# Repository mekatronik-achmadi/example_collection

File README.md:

Examples collection from various works

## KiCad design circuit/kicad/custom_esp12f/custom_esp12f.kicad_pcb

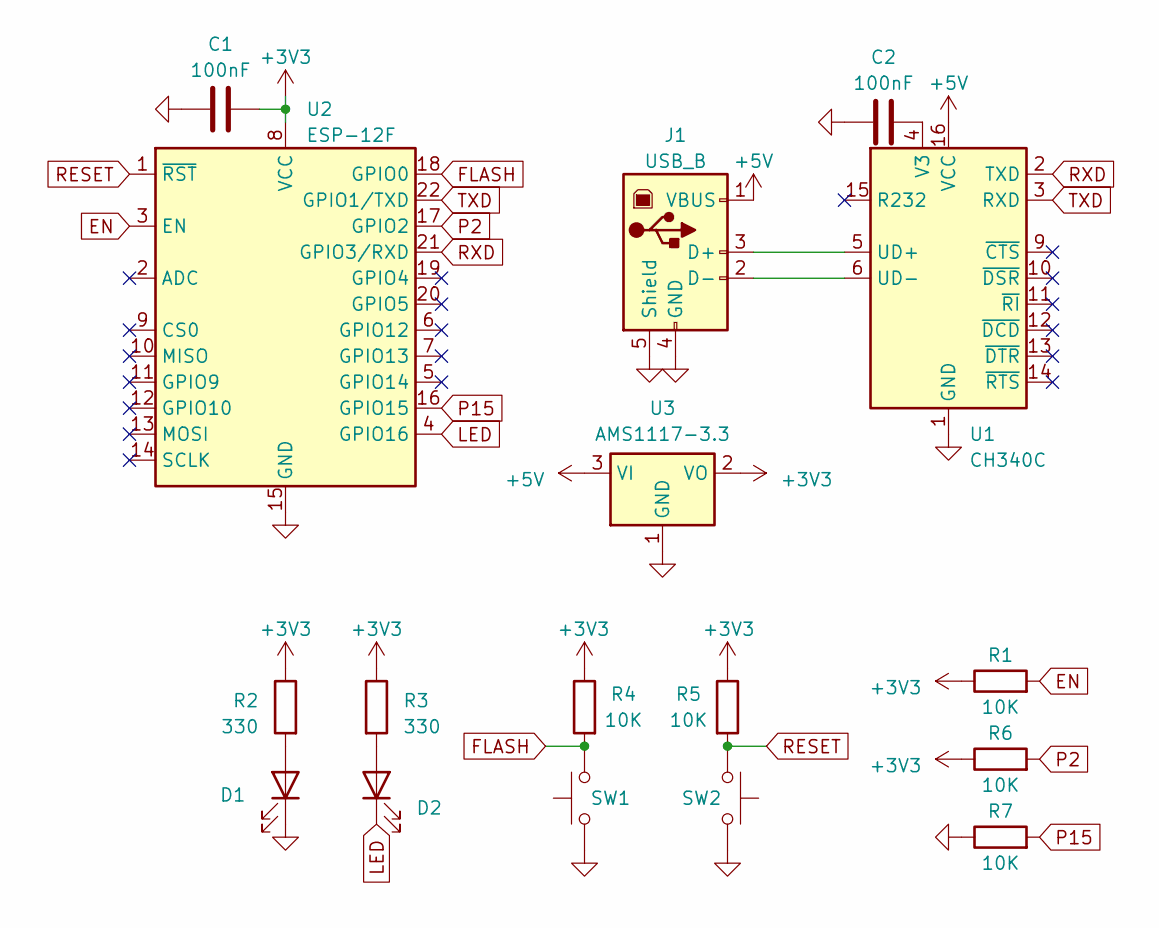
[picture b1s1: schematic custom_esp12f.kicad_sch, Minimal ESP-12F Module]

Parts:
C1, C2: 100nF; C_0805_2012Metric_Pad1.18x1.45mm_HandSolder
D1: MERAH; LED_0805_2012Metric_Pad1.15x1.40mm_HandSolder
D2: HIJAU; LED_0805_2012Metric_Pad1.15x1.40mm_HandSolder
J1: USB_B; USB_B_Lumberg_2411_02_Horizontal
R1, R4, R5, R6, R7: 10K; R_0805_2012Metric
R2, R3: 330; R_0805_2012Metric
SW1, SW2: SW_Push; SW_PUSH_6mm
U1: CH340C; SOIC-16_3.9x9.9mm_P1.27mm
U2: ESP-12F; ESP-12E
U3: AMS1117-3.3; SOT-223-3_TabPin2

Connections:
+3V3: C1.2, R1.1, R2.1, R3.1, R4.1, R5.1, R6.1, U2.8 (VCC), U3.2 (VO)
+5V: J1.1 (VBUS), U1.16 (VCC), U3.3 (VI)
EN: R1.2, U2.3 (EN)
FLASH: R4.2, SW1.1, U2.18 (GPIO0)
GND: C1.1, C2.1, D1.1 (K), J1.4 (GND), J1.5 (Shield), R7.1, SW1.2, SW2.2, U1.1 (GND), U2.15 (GND), U3.1 (GND)
LED: D2.1 (K), U2.4 (GPIO16)
unnamed: D1.2 (A), R2.2
unnamed: D2.2 (A), R3.2
unnamed: J1.3 (D+), U1.5 (UD+)
unnamed: J1.2 (D-), U1.6 (UD-)
unnamed: C2.2, U1.4 (V3)
P2: R6.2, U2.17 (GPIO2)
P15: R7.2, U2.16 (GPIO15)
RESET: R5.2, SW2.1, U2.1 (~RST)
RXD: U1.2 (TXD), U2.21 (GPIO3/RXD)
TXD: U1.3 (RXD), U2.22 (GPIO1/TXD)

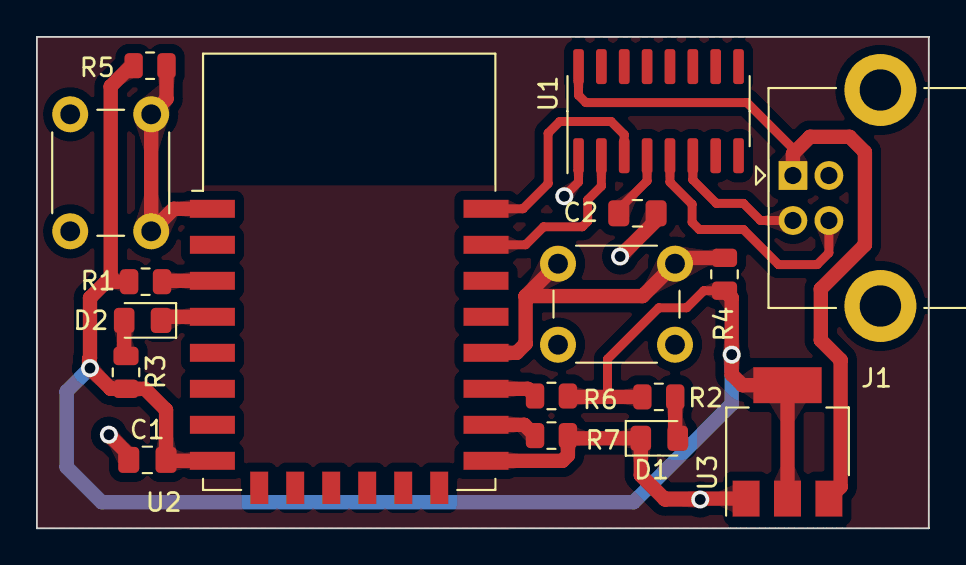
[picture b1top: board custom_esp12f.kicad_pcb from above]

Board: 2 copper layers, 49.5 x 27.3 mm, 17 parts (0 on the bottom side), 16 nets.

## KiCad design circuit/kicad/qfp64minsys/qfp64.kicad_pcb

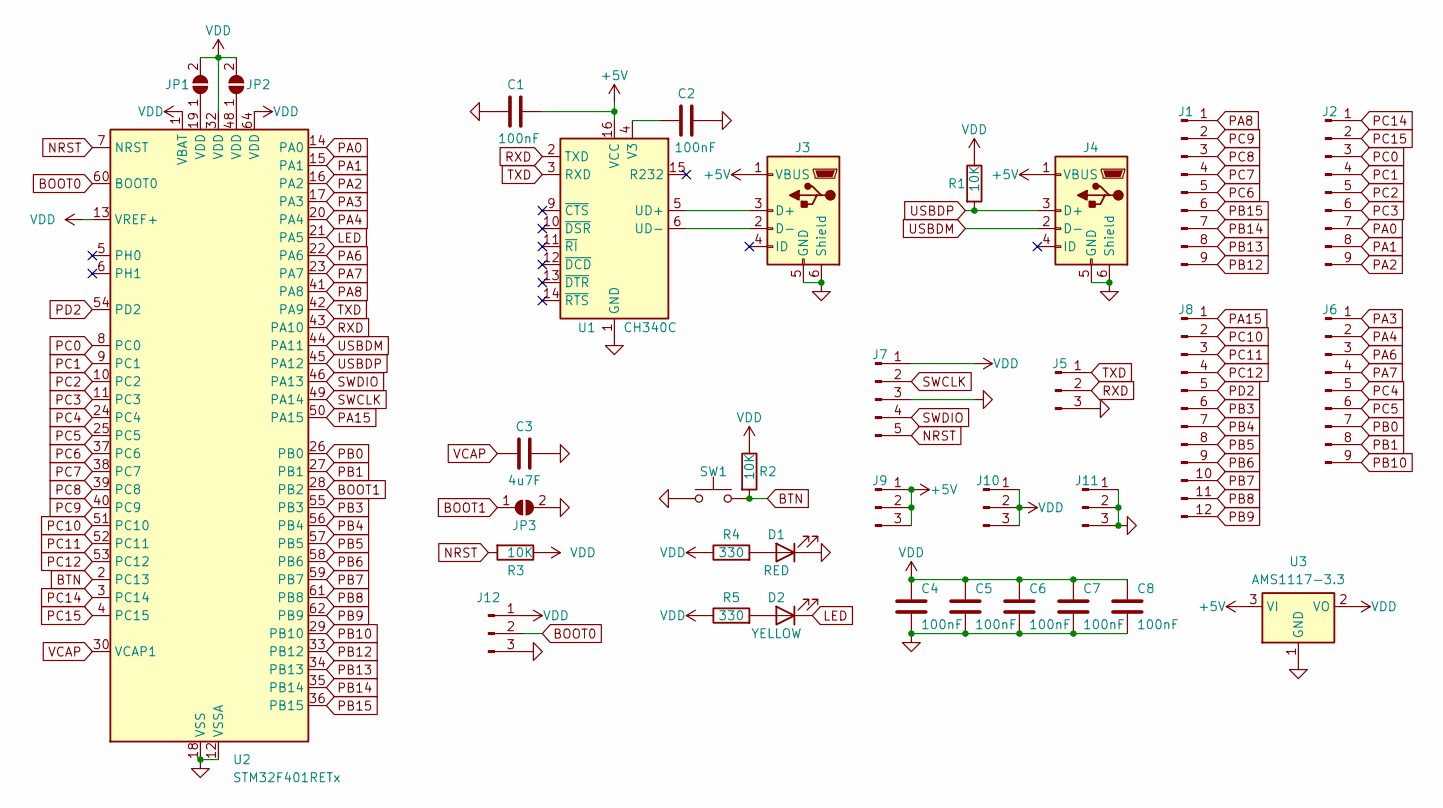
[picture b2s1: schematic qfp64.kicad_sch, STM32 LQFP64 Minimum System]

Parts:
C1, C2, C4, C5, C6, C7, C8: 100nF; C_0805_2012Metric_Pad1.18x1.45mm_HandSolder
C3: 4u7F; CP_EIA-3216-18_Kemet-A
D1: RED; LED_0805_2012Metric_Pad1.15x1.40mm_HandSolder
D2: YELLOW; LED_0805_2012Metric_Pad1.15x1.40mm_HandSolder
J1, J2, J6: Conn_01x09_Pin; PinHeader_1x09_P2.54mm_Vertical
J3, J4: USB_B_Mini; USB_Mini-B_Wuerth_65100516121_Horizontal
J5, J9, J10, J11, J12: Conn_01x03_Pin; PinHeader_1x03_P2.54mm_Vertical
J7: Conn_01x05_Pin; PinHeader_1x05_P2.54mm_Vertical
J8: Conn_01x12_Pin; PinHeader_1x12_P2.54mm_Vertical
JP1, JP2, JP3: SolderJumper_2_Open; SolderJumper-2_P1.3mm_Open_RoundedPad1.0x1.5mm
R1, R2, R3: 10K; R_0805_2012Metric_Pad1.20x1.40mm_HandSolder
R4, R5: 330; R_0805_2012Metric_Pad1.20x1.40mm_HandSolder
SW1: SW_Push; SW_PUSH_6mm
U1: CH340C; SOIC-16_3.9x9.9mm_P1.27mm
U2: STM32F401RETx; LQFP-64_10x10mm_P0.5mm
U3: AMS1117-3.3; SOT-223-3_TabPin2

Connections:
+5V: C1.1, J3.1 (VBUS), J4.1 (VBUS), J9.1, J9.2, J9.3, U1.16 (VCC), U3.3 (VI)
BOOT0: J12.2, U2.60 (BOOT0)
BOOT1: JP3.1 (A), U2.28 (PB2)
BTN: R2.2, SW1.2, U2.2 (PC13)
GND: C1.2, C2.2, C3.2, C4.2, C5.2, C6.2, C7.2, C8.2, D1.1 (K), J3.5 (GND), J3.6 (Shield), J4.5 (GND), J4.6 (Shield), J5.3, J7.3, J11.1, J11.2, J11.3, J12.3, JP3.2 (B), SW1.1, U1.1 (GND), U2.12 (VSSA), U2.18 (VSS), U2.31 (VSS), U2.47 (VSS), U2.63 (VSS), U3.1 (GND)
LED: D2.1 (K), U2.21 (PA5)
NRST: J7.5, R3.2, U2.7 (NRST)
unnamed: D1.2 (A), R4.2
unnamed: D2.2 (A), R5.2
unnamed: J3.3 (D+), U1.5 (UD+)
unnamed: J3.2 (D-), U1.6 (UD-)
unnamed: JP1.1 (A), U2.19 (VDD)
unnamed: JP2.1 (A), U2.48 (VDD)
unnamed: C2.1, U1.4 (V3)
PA0: J2.7, U2.14 (PA0)
PA1: J2.8, U2.15 (PA1)
PA2: J2.9, U2.16 (PA2)
PA3: J6.1, U2.17 (PA3)
PA4: J6.2, U2.20 (PA4)
PA6: J6.3, U2.22 (PA6)
PA7: J6.4, U2.23 (PA7)
PA8: J1.1, U2.41 (PA8)
PA15: J8.1, U2.50 (PA15)
PB0: J6.7, U2.26 (PB0)
PB1: J6.8, U2.27 (PB1)
PB3: J8.6, U2.55 (PB3)
PB4: J8.7, U2.56 (PB4)
PB5: J8.8, U2.57 (PB5)
PB6: J8.9, U2.58 (PB6)
PB7: J8.10, U2.59 (PB7)
PB8: J8.11, U2.61 (PB8)
PB9: J8.12, U2.62 (PB9)
PB10: J6.9, U2.29 (PB10)
PB12: J1.9, U2.33 (PB12)
PB13: J1.8, U2.34 (PB13)
PB14: J1.7, U2.35 (PB14)
PB15: J1.6, U2.36 (PB15)
PC0: J2.3, U2.8 (PC0)
PC1: J2.4, U2.9 (PC1)
PC2: J2.5, U2.10 (PC2)
PC3: J2.6, U2.11 (PC3)
PC4: J6.5, U2.24 (PC4)
PC5: J6.6, U2.25 (PC5)
PC6: J1.5, U2.37 (PC6)
PC7: J1.4, U2.38 (PC7)
PC8: J1.3, U2.39 (PC8)
PC9: J1.2, U2.40 (PC9)
PC10: J8.2, U2.51 (PC10)
PC11: J8.3, U2.52 (PC11)
PC12: J8.4, U2.53 (PC12)
PC14: J2.1, U2.3 (PC14)
PC15: J2.2, U2.4 (PC15)
PD2: J8.5, U2.54 (PD2)
RXD: J5.2, U1.2 (TXD), U2.43 (PA10)
SWCLK: J7.2, U2.49 (PA14)
SWDIO: J7.4, U2.46 (PA13)
TXD: J5.1, U1.3 (RXD), U2.42 (PA9)
USBDM: J4.2 (D-), U2.44 (PA11)
USBDP: J4.3 (D+), R1.2, U2.45 (PA12)
VCAP: C3.1, U2.30 (VCAP1)
VDD: C4.1, C5.1, C6.1, C7.1, C8.1, J7.1, J10.1, J10.2, J10.3, J12.1, JP1.2 (B), JP2.2 (B), R1.1, R2.1, R3.1, R4.1, R5.1, U2.1 (VBAT), U2.13 (VREF+), U2.32 (VDD), U2.64 (VDD), U3.2 (VO)

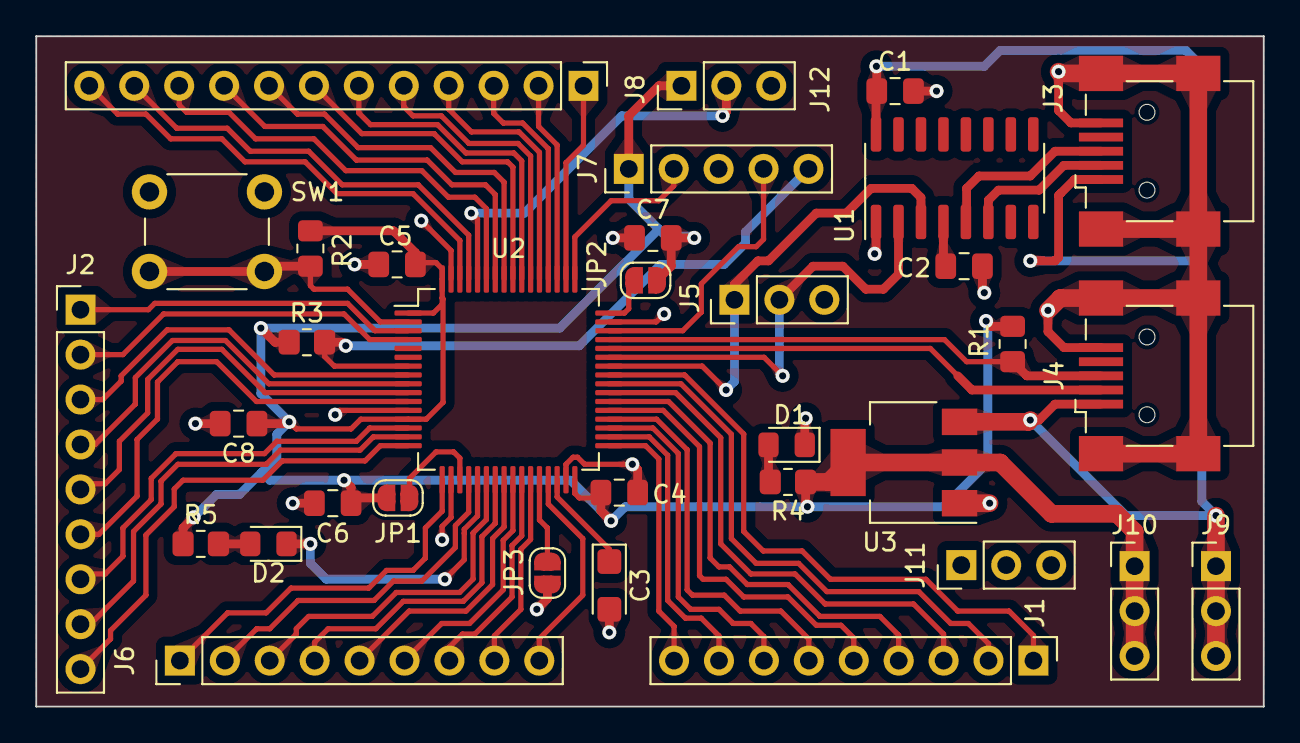
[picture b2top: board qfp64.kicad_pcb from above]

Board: 2 copper layers, 69.4 x 37.9 mm, 34 parts (0 on the bottom side), 61 nets.

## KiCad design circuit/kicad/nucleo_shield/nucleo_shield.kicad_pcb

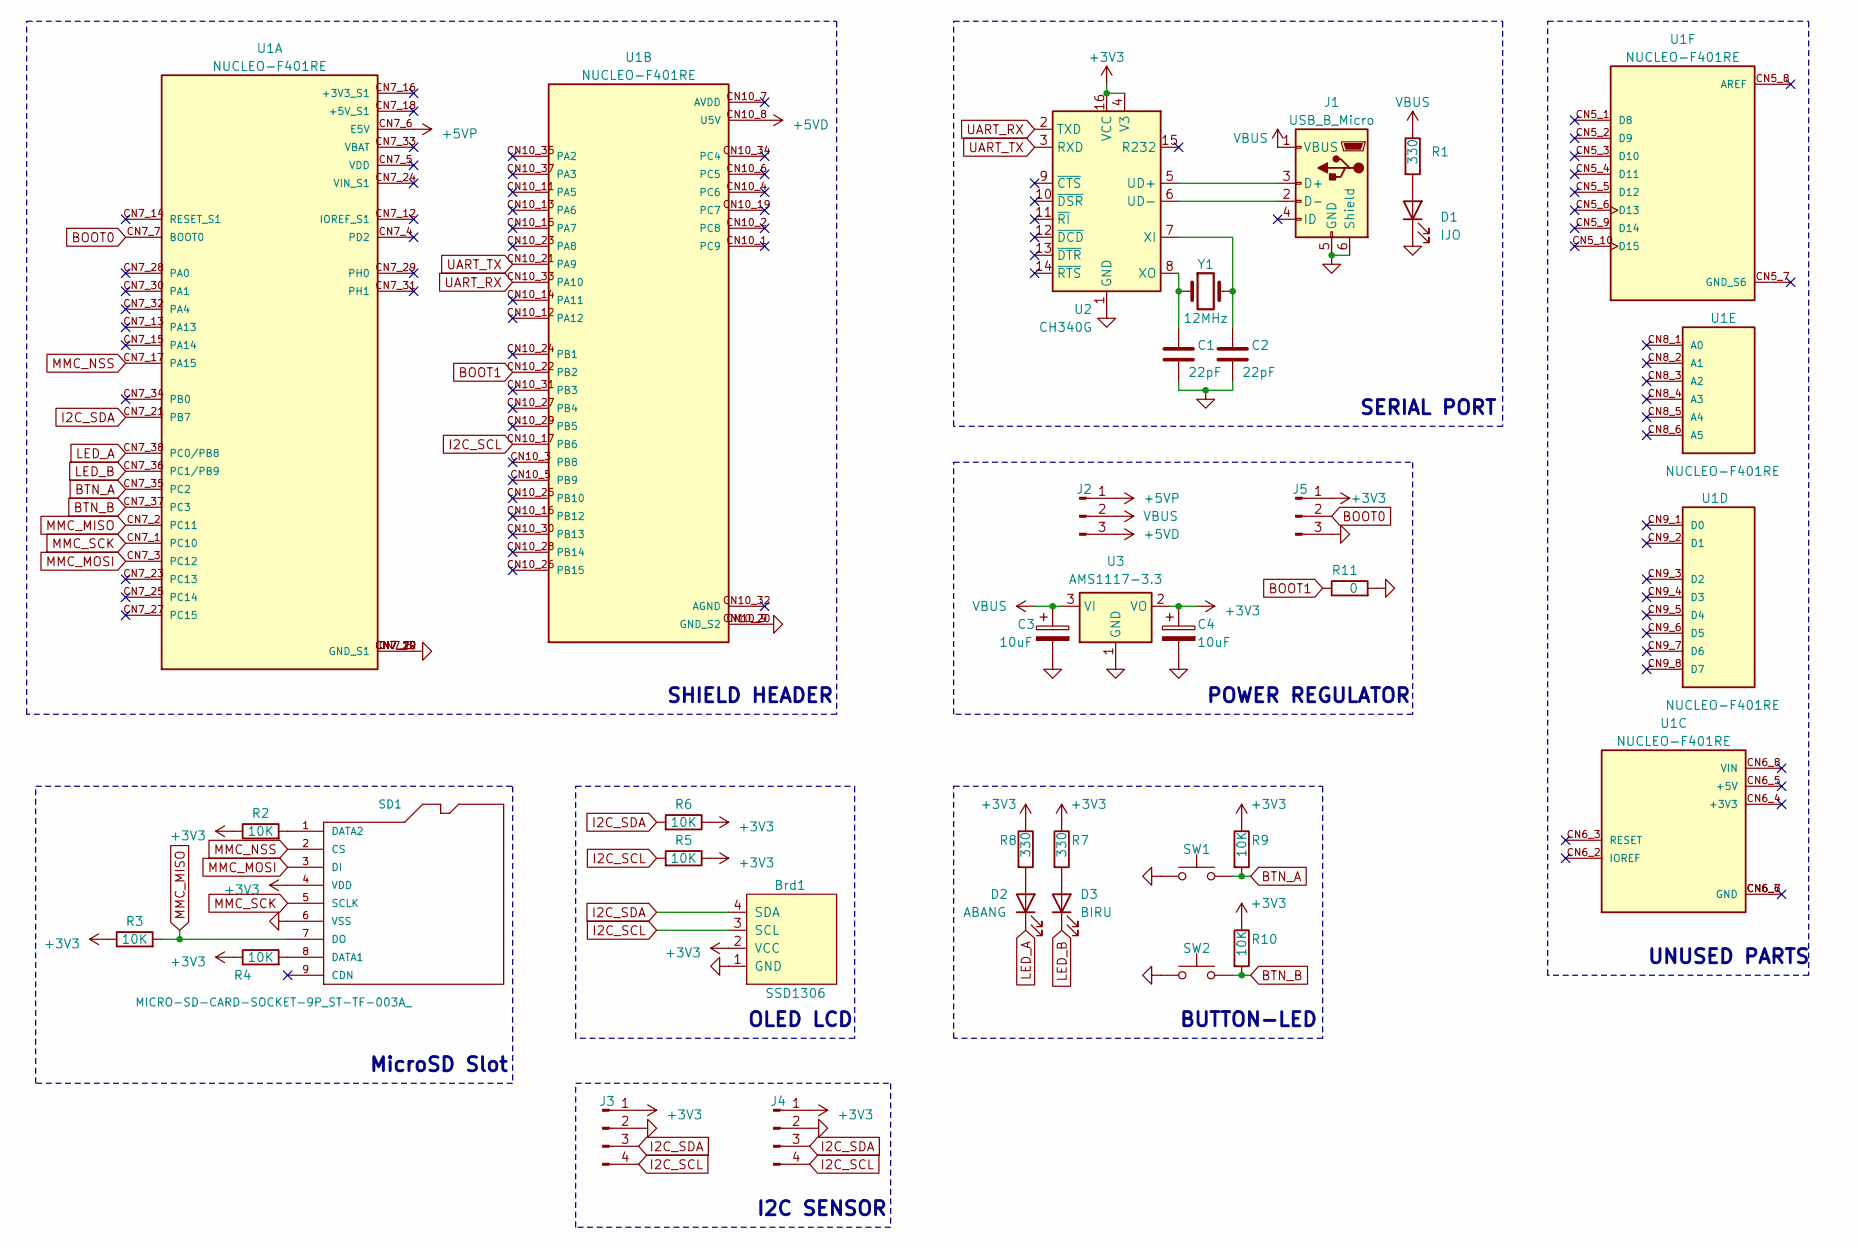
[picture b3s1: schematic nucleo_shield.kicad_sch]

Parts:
Brd1: SSD1306; 128x64OLED
C1, C2: 22pF; C_0805_2012Metric_Pad1.18x1.45mm_HandSolder
C3, C4: 10uF; CP_Elec_4x5.3
D1: IJO; LED_0805_2012Metric_Pad1.15x1.40mm_HandSolder
D2: ABANG; LED_0805_2012Metric_Pad1.15x1.40mm_HandSolder
D3: BIRU; LED_0805_2012Metric_Pad1.15x1.40mm_HandSolder
J1: USB_B_Micro; USB_Micro-B_Wuerth_629105150521
J2, J5: Conn_01x03_Pin; PinHeader_1x03_P2.54mm_Vertical
J3, J4: Conn_01x04_Pin; PinHeader_1x04_P2.54mm_Vertical
R1, R7, R8: 330; R_0805_2012Metric_Pad1.20x1.40mm_HandSolder
R2, R3, R4, R5, R6, R9, R10: 10K; R_0805_2012Metric_Pad1.20x1.40mm_HandSolder
R11: 0; R_0805_2012Metric_Pad1.20x1.40mm_HandSolder
SD1: MICRO-SD-CARD-SOCKET-9P_ST-TF-003A_; MICRO-SD9+4P-SMD-16.1X14.5X1.85MM; MPN ST-TF-003A
SW1, SW2: SW_Push; SW_PUSH_6mm
U1: NUCLEO-F401RE; ST_NUCLEO-F401RE; PARTREV 13
U2: CH340G; SOIC-16_3.9x9.9mm_P1.27mm
U3: AMS1117-3.3; SOT-223-3_TabPin2
Y1: 12MHz; Crystal_HC49-4H_Vertical

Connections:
+3V3: Brd1.2 (VCC), C4.1, J3.1, J4.1, J5.1, R2.1, R3.1, R4.1, R5.1, R6.1, R7.1, R8.1, R9.1, R10.1, SD1.4 (VDD), U2.4 (V3), U2.16 (VCC), U3.2 (VO)
+5VD: J2.3, U1.CN10_8 (U5V)
+5VP: J2.1, U1.CN7_6 (E5V)
BOOT0: J5.2, U1.CN7_7 (BOOT0)
BOOT1: R11.1, U1.CN10_22 (PB2)
BTN_A: R9.2, SW1.2, U1.CN7_35 (PC2)
BTN_B: R10.2, SW2.2, U1.CN7_37 (PC3)
GND: Brd1.1 (GND), C1.2, C2.2, C3.2, C4.2, D1.1 (K), J1.5 (GND), J1.6 (Shield), J3.2, J4.2, J5.3, R11.2, SD1.6 (VSS), SW1.1, SW2.1, U1.CN7_8 (GND_S1), U1.CN7_19 (GND_S1), U1.CN7_20 (GND_S1), U1.CN7_22 (GND_S1), U1.CN10_9 (GND_S2), U1.CN10_20 (GND_S2), U2.1 (GND), U3.1 (GND)
I2C_SCL: Brd1.3 (SCL), J3.4, J4.4, R5.2, U1.CN10_17 (PB6)
I2C_SDA: Brd1.4 (SDA), J3.3, J4.3, R6.2, U1.CN7_21 (PB7)
LED_A: D2.1 (K), U1.CN7_38 (PC0/PB8)
LED_B: D3.1 (K), U1.CN7_36 (PC1/PB9)
MMC_MISO: R3.2, SD1.7 (DO), U1.CN7_2 (PC11)
MMC_MOSI: SD1.3 (DI), U1.CN7_3 (PC12)
MMC_NSS: SD1.2 (CS), U1.CN7_17 (PA15)
MMC_SCK: SD1.5 (SCLK), U1.CN7_1 (PC10)
unnamed: D1.2 (A), R1.2
unnamed: D2.2 (A), R8.2
unnamed: D3.2 (A), R7.2
unnamed: J1.3 (D+), U2.5 (UD+)
unnamed: J1.2 (D-), U2.6 (UD-)
unnamed: R4.2, SD1.8 (DATA1)
unnamed: R2.2, SD1.1 (DATA2)
unnamed: C2.1, U2.7 (XI), Y1.2
unnamed: C1.1, U2.8 (XO), Y1.1
UART_RX: U1.CN10_33 (PA10), U2.2 (TXD)
UART_TX: U1.CN10_21 (PA9), U2.3 (RXD)
VBUS: C3.1, J1.1 (VBUS), J2.2, R1.1, U3.3 (VI)

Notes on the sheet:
BUTTON-LED
I2C SENSOR
MicroSD Slot
UNUSED PARTS
SHIELD HEADER
POWER REGULATOR
OLED LCD
SERIAL PORT

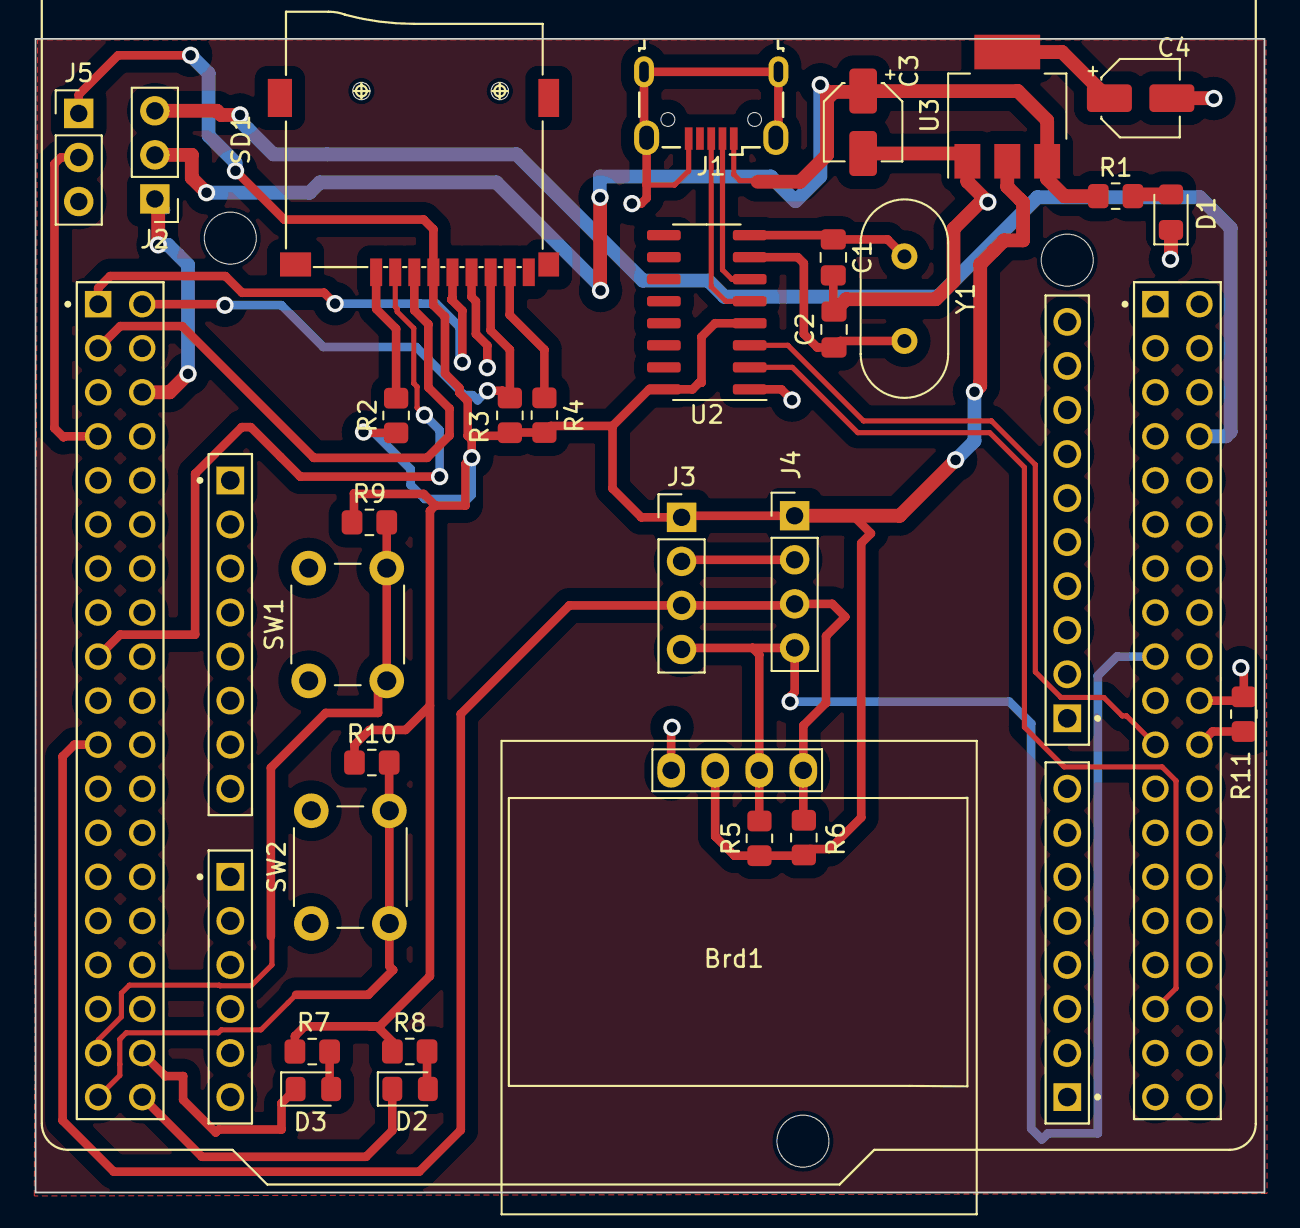
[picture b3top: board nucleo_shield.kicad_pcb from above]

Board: 2 copper layers, 70.9 x 66.5 mm, 31 parts (0 on the bottom side), 28 nets.

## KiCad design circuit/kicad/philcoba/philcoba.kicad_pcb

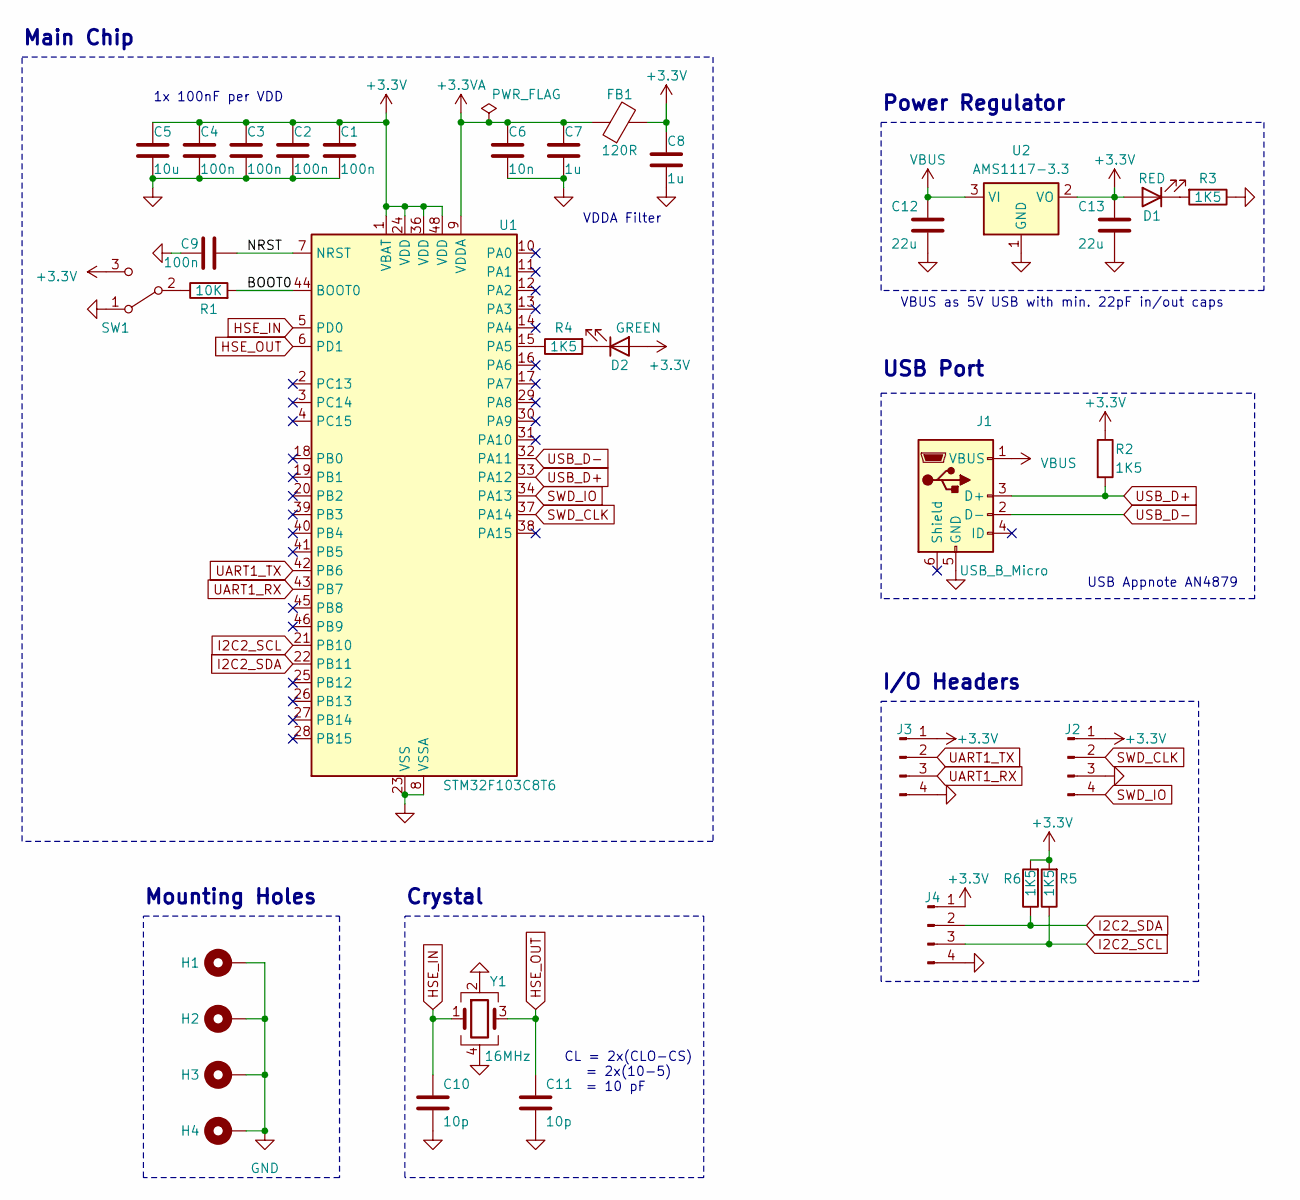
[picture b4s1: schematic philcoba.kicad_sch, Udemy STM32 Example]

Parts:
C1, C2, C3, C4, C9: 100n; C_0603_1608Metric
C5: 10u; C_0603_1608Metric
C6: 10n; C_0603_1608Metric
C7, C8: 1u; C_0603_1608Metric
C10, C11: 10p; C_0603_1608Metric
C12, C13: 22u; C_0603_1608Metric
D1: RED; LED_0805_2012Metric
D2: GREEN; LED_0805_2012Metric
FB1: 120R; L_0603_1608Metric
H1, H2, H3, H4: MountingHole_Pad; MountingHole_2.5mm_Pad_Via
J1: USB_B_Micro; USB_Micro-B_Wuerth_629105150521
J2, J3, J4: Conn_01x04_Pin; PinHeader_1x04_P2.54mm_Vertical
R1: 10K; R_0603_1608Metric
R2, R3, R4, R5, R6: 1K5; R_0603_1608Metric
SW1: SW_SPDT; SW_SPDT_PCM12
U1: STM32F103C8T6; LQFP-48_7x7mm_P0.5mm
U2: AMS1117-3.3; SOT-223-3_TabPin2
Y1: 16MHz; Crystal_SMD_3225-4Pin_3.2x2.5mm

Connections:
+3.3V: C1.1, C2.1, C3.1, C4.1, C5.1, C8.1, C13.1, D1.2 (A), D2.2 (A), FB1.2, J2.1, J3.1, J4.1, R2.1, R5.2, R6.2, SW1.3 (C), U1.1 (VBAT), U1.24 (VDD), U1.36 (VDD), U1.48 (VDD), U2.2 (VO)
+3.3VA: C6.1, C7.1, FB1.1, U1.9 (VDDA)
/BOOT0: R1.2, U1.44 (BOOT0)
/NRST: C9.2, U1.7 (NRST)
GND: C1.2, C2.2, C3.2, C4.2, C5.2, C6.2, C7.2, C8.2, C9.1, C10.2, C11.2, C12.2, C13.2, H1.1, H2.1, H3.1, H4.1, J1.5 (GND), J2.3, J3.4, J4.4, R3.1, SW1.1 (A), U1.8 (VSSA), U1.23 (VSS), U1.35 (VSS), U1.47 (VSS), U2.1 (GND), Y1.2, Y1.4
HSE_IN: C10.1, U1.5 (PD0), Y1.1
HSE_OUT: C11.1, U1.6 (PD1), Y1.3
I2C2_SCL: J4.3, R5.1, U1.21 (PB10)
I2C2_SDA: J4.2, R6.1, U1.22 (PB11)
unnamed: D1.1 (K), R3.2
unnamed: D2.1 (K), R4.2
unnamed: R1.1, SW1.2 (B)
unnamed: R4.1, U1.15 (PA5)
SWD_CLK: J2.2, U1.37 (PA14)
SWD_IO: J2.4, U1.34 (PA13)
UART1_RX: J3.3, U1.43 (PB7)
UART1_TX: J3.2, U1.42 (PB6)
USB_D+: J1.3 (D+), R2.2, U1.33 (PA12)
USB_D-: J1.2 (D-), U1.32 (PA11)
VBUS: C12.1, J1.1 (VBUS), U2.3 (VI)

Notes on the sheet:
CL = 2x(CLO-CS) = 2x(10-5) = 10 pF
VDDA Filter
Mounting Holes
USB Appnote AN4879
Power Regulator
Main Chip
VBUS as 5V USB with min. 22pF in/out caps
I/O Headers
1x 100nF per VDD
Crystal
USB Port

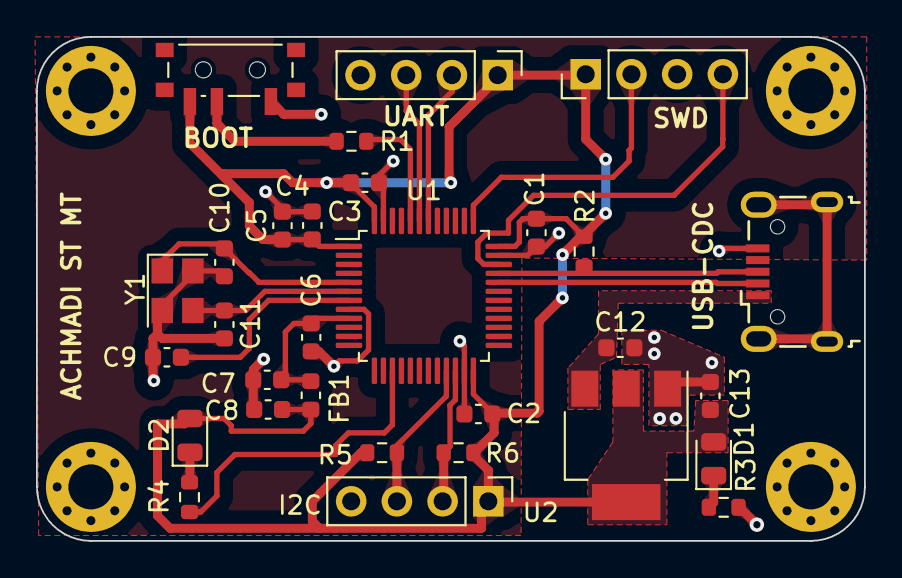
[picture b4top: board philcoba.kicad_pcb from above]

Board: 2 copper layers, 46.0 x 28.0 mm, 34 parts (0 on the bottom side), 20 nets.

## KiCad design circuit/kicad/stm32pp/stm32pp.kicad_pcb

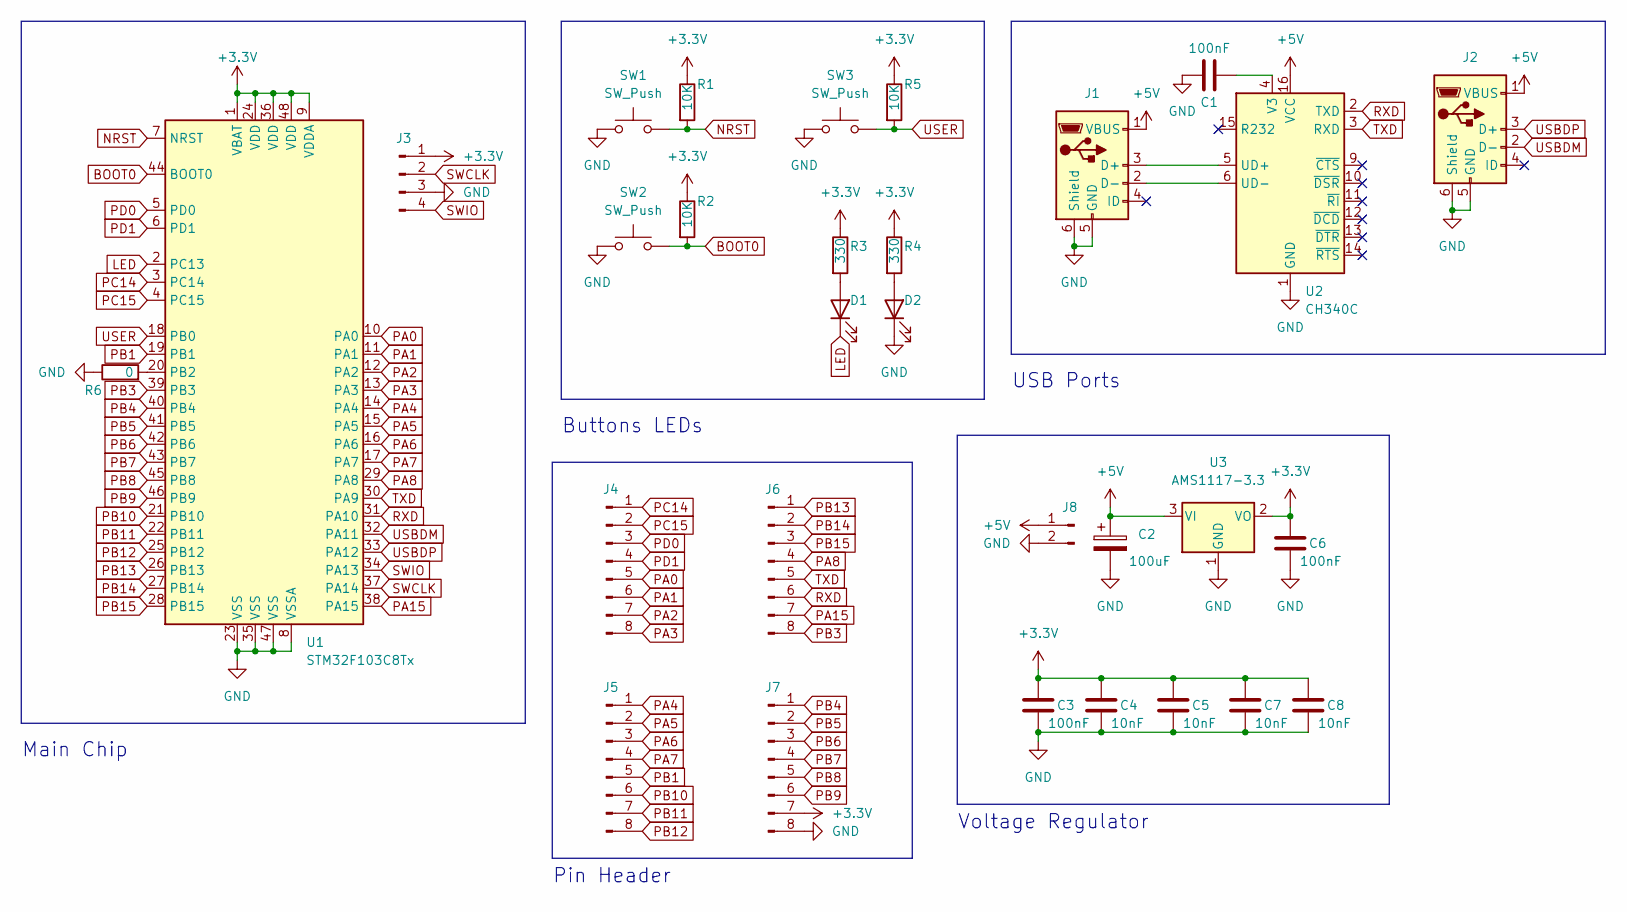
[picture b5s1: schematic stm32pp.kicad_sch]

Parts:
C1, C3, C6: 100nF; C_0603_1608Metric
C2: 100uF; CP_Elec_3x5.3
C4, C5, C7, C8: 10nF; C_0603_1608Metric
D1, D2: LED; LED_0805_2012Metric
J1, J2: USB_B_Micro; USB_Micro-B_Wuerth_629105150521
J3: Conn_01x04_Male; PinHeader_1x04_P2.54mm_Vertical
J4, J5, J6, J7: Conn_01x08_Male; PinHeader_1x08_P2.54mm_Vertical
J8: Conn_01x02_Male; PinHeader_1x02_P2.54mm_Vertical
R1, R2, R5: 10K; R_0603_1608Metric
R3, R4: 330; R_0603_1608Metric
R6: 0; R_0603_1608Metric
SW1, SW2, SW3: SW_Push; SW_SPST_B3U-1000P-B
U1: STM32F103C8Tx; LQFP-48_7x7mm_P0.5mm
U2: CH340C; SOIC-16_3.9x9.9mm_P1.27mm
U3: AMS1117-3.3; SOT-223-3_TabPin2

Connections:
+3.3V: C3.1, C4.1, C5.1, C6.1, C7.1, C8.1, J3.1, J7.7, R1.1, R2.1, R3.1, R4.1, R5.1, U1.1 (VBAT), U1.9 (VDDA), U1.24 (VDD), U1.36 (VDD), U1.48 (VDD), U3.2 (VO)
+5V: C2.1, J1.1 (VBUS), J2.1 (VBUS), J8.1, U2.16 (VCC), U3.3 (VI)
BOOT0: R2.2, SW2.2, U1.44 (BOOT0)
GND: C1.1, C2.2, C3.2, C4.2, C5.2, C6.2, C7.2, C8.2, D2.1 (K), J1.5 (GND), J1.6 (Shield), J2.5 (GND), J2.6 (Shield), J3.3, J7.8, J8.2, R6.1, SW1.1, SW2.1, SW3.1, U1.8 (VSSA), U1.23 (VSS), U1.35 (VSS), U1.47 (VSS), U2.1 (GND), U3.1 (GND)
LED: D1.1 (K), U1.2 (PC13)
NRST: R1.2, SW1.2, U1.7 (NRST)
unnamed: C1.2, U2.4 (V3)
unnamed: D1.2 (A), R3.2
unnamed: D2.2 (A), R4.2
unnamed: J1.2 (D-), U2.6 (UD-)
unnamed: J1.3 (D+), U2.5 (UD+)
unnamed: R6.2, U1.20 (PB2)
PA0: J4.5, U1.10 (PA0)
PA1: J4.6, U1.11 (PA1)
PA2: J4.7, U1.12 (PA2)
PA3: J4.8, U1.13 (PA3)
PA4: J5.1, U1.14 (PA4)
PA5: J5.2, U1.15 (PA5)
PA6: J5.3, U1.16 (PA6)
PA7: J5.4, U1.17 (PA7)
PA8: J6.4, U1.29 (PA8)
PA15: J6.7, U1.38 (PA15)
PB1: J5.5, U1.19 (PB1)
PB3: J6.8, U1.39 (PB3)
PB4: J7.1, U1.40 (PB4)
PB5: J7.2, U1.41 (PB5)
PB6: J7.3, U1.42 (PB6)
PB7: J7.4, U1.43 (PB7)
PB8: J7.5, U1.45 (PB8)
PB9: J7.6, U1.46 (PB9)
PB10: J5.6, U1.21 (PB10)
PB11: J5.7, U1.22 (PB11)
PB12: J5.8, U1.25 (PB12)
PB13: J6.1, U1.26 (PB13)
PB14: J6.2, U1.27 (PB14)
PB15: J6.3, U1.28 (PB15)
PC14: J4.1, U1.3 (PC14)
PC15: J4.2, U1.4 (PC15)
PD0: J4.3, U1.5 (PD0)
PD1: J4.4, U1.6 (PD1)
RXD: J6.6, U1.31 (PA10), U2.2 (TXD)
SWCLK: J3.2, U1.37 (PA14)
SWIO: J3.4, U1.34 (PA13)
TXD: J6.5, U1.30 (PA9), U2.3 (RXD)
USBDM: J2.2 (D-), U1.32 (PA11)
USBDP: J2.3 (D+), U1.33 (PA12)
USER: R5.2, SW3.2, U1.18 (PB0)

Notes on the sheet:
Voltage Regulator
Main Chip
Buttons LEDs
USB Ports
Pin Header

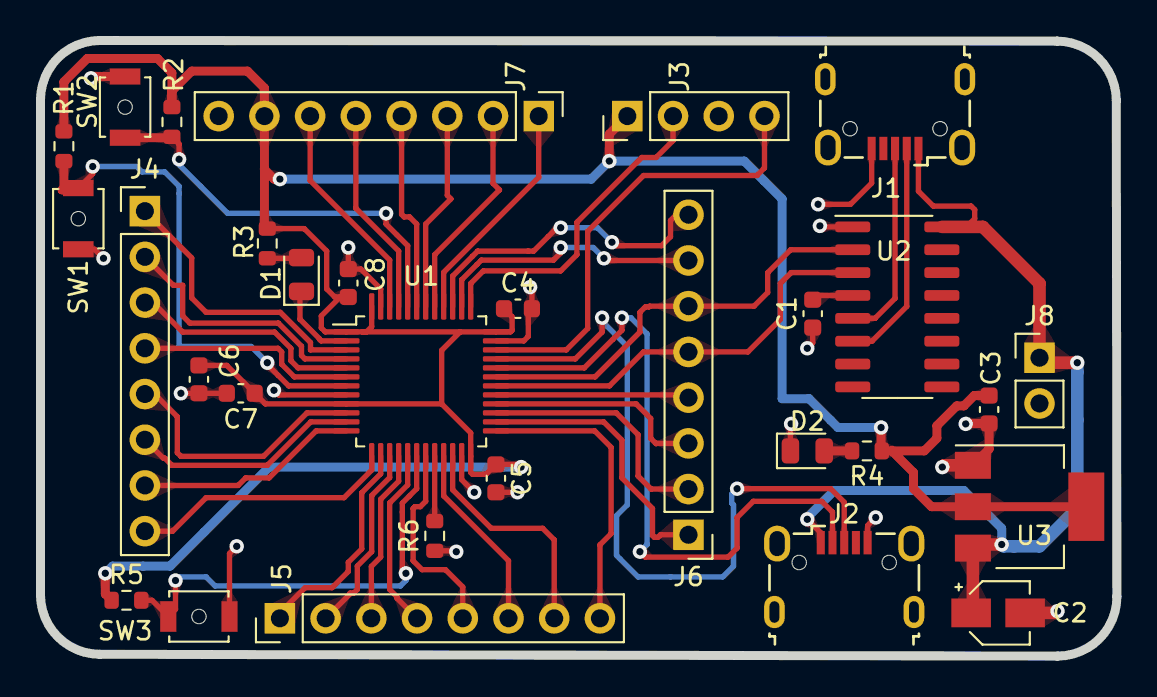
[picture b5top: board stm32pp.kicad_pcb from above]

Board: 2 copper layers, 59.8 x 34.2 mm, 30 parts (0 on the bottom side), 47 nets.

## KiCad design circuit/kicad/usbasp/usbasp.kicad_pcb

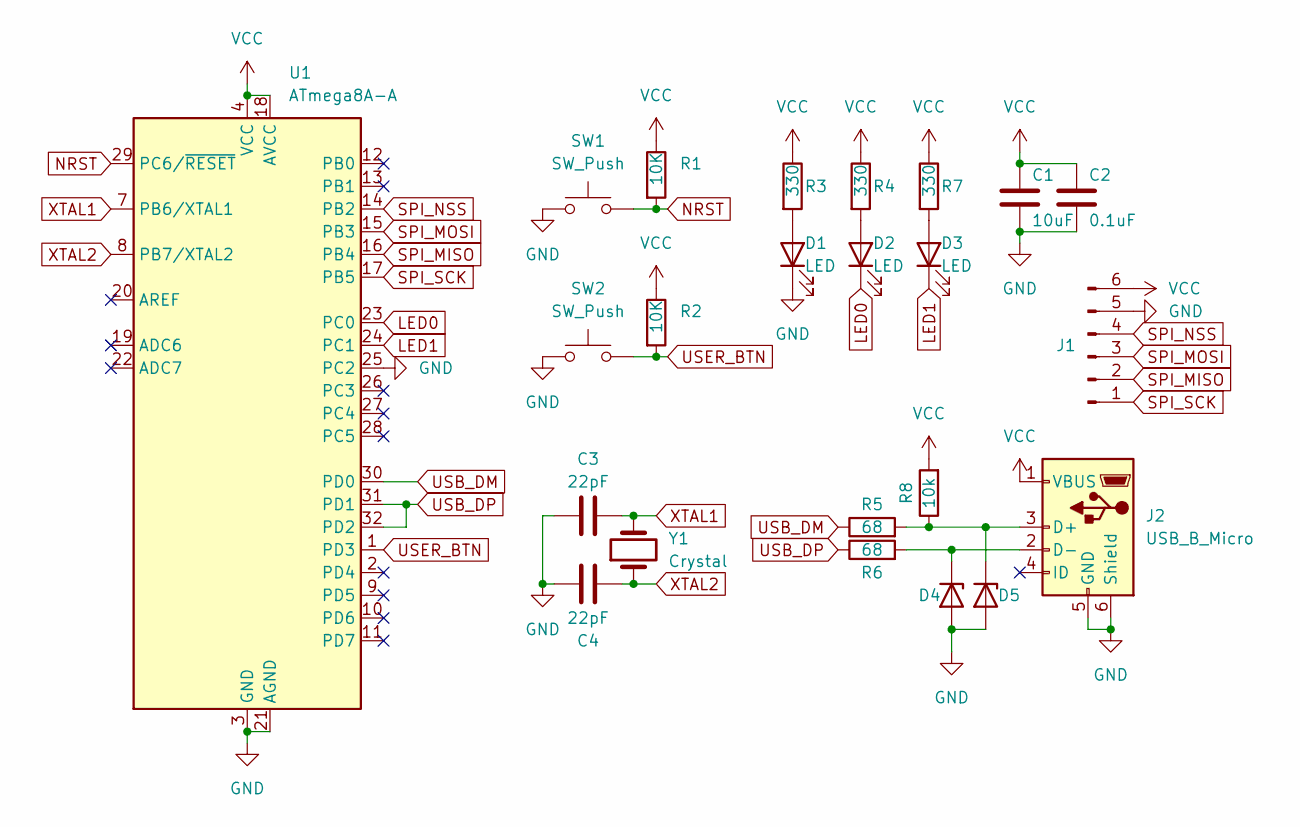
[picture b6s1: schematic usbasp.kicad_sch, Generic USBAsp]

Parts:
C1: 10uF; C_0805_2012Metric_Pad1.18x1.45mm_HandSolder
C2: 0.1uF; C_0805_2012Metric_Pad1.18x1.45mm_HandSolder
C3, C4: 22pF; C_0805_2012Metric_Pad1.18x1.45mm_HandSolder
D1, D2, D3: LED; LED_0805_2012Metric_Pad1.15x1.40mm_HandSolder
D4, D5: DZ-3v3; D_MiniMELF_Handsoldering
J1: Conn_01x06_Male; PinHeader_1x06_P2.54mm_Horizontal
J2: USB_B_Micro; USB_Micro-B_Wuerth_629105150521
R1, R2: 10K; R_0805_2012Metric_Pad1.20x1.40mm_HandSolder
R3, R4, R7: 330; R_0805_2012Metric_Pad1.20x1.40mm_HandSolder
R5, R6: 68; R_0805_2012Metric_Pad1.20x1.40mm_HandSolder
R8: 10k; R_0805_2012Metric_Pad1.20x1.40mm_HandSolder
SW1, SW2: SW_Push; SW_PUSH_6mm
U1: ATmega8A-A; TQFP-32_7x7mm_P0.8mm
Y1: Crystal; Crystal_HC49-4H_Vertical

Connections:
GND: C1.2, C2.2, C3.1, C4.1, D1.1 (K), D4.2 (A), D5.2 (A), J1.5, J2.5 (GND), J2.6 (Shield), SW1.1, SW2.1, U1.3 (GND), U1.5 (GND), U1.21 (AGND), U1.25 (PC2)
LED0: D2.1 (K), U1.23 (PC0)
LED1: D3.1 (K), U1.24 (PC1)
NRST: R1.2, SW1.2, U1.29 (PC6/~RESET)
unnamed: D1.2 (A), R3.2
unnamed: D2.2 (A), R4.2
unnamed: D3.2 (A), R7.2
unnamed: D4.1 (K), J2.2 (D-), R6.2
unnamed: D5.1 (K), J2.3 (D+), R5.2, R8.1
SPI_MISO: J1.2, U1.16 (PB4)
SPI_MOSI: J1.3, U1.15 (PB3)
SPI_NSS: J1.4, U1.14 (PB2)
SPI_SCK: J1.1, U1.17 (PB5)
USB_DM: R5.1, U1.30 (PD0)
USB_DP: R6.1, U1.31 (PD1), U1.32 (PD2)
USER_BTN: R2.2, SW2.2, U1.1 (PD3)
VCC: C1.1, C2.1, J1.6, J2.1 (VBUS), R1.1, R2.1, R3.1, R4.1, R7.1, R8.2, U1.4 (VCC), U1.6 (VCC), U1.18 (AVCC)
XTAL1: C3.2, U1.7 (PB6/XTAL1), Y1.2
XTAL2: C4.2, U1.8 (PB7/XTAL2), Y1.1

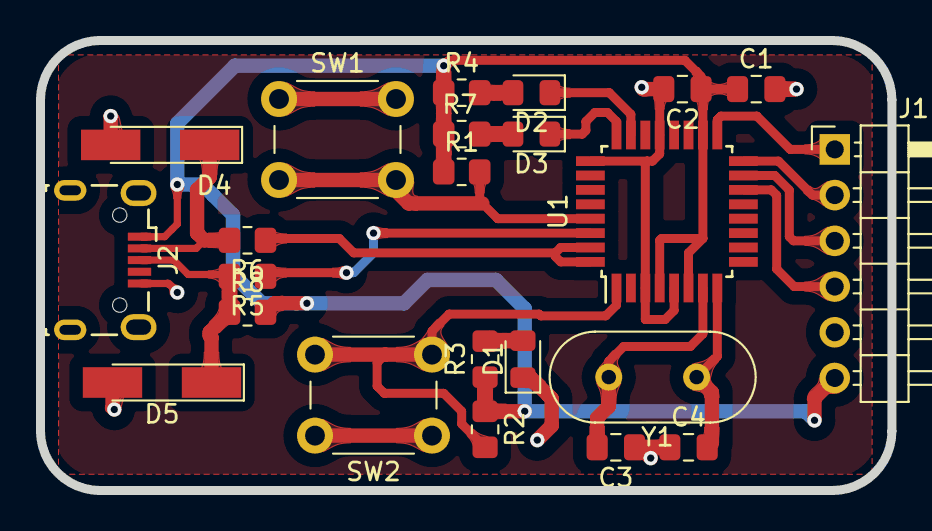
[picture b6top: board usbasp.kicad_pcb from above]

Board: 2 copper layers, 47.3 x 25.0 mm, 23 parts (0 on the bottom side), 19 nets.
